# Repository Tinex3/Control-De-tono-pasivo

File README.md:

# Control de Tono para Canales de Audio R y L

## Descripción

Proyecto básico de control de tono discreto para los canales de audio derecho (R) e izquierdo (L). Utiliza resistencias, condensadores, potenciómetros y conectores JST XH para ajustes simples de bajos, agudos y volumen en dispositivos de audio.

## Componentes

- Resistencias
- Condensadores
- Potenciómetros
- Conectores JST XH

## Uso

Ajusta fácilmente los niveles de bajos, agudos y volumen general.

## Autor

- Autor: Benjamin Riquelme
- Correo electrónico: b.riquelme.gomez@gmail.com

## Licencia

Licencia MIT. Consulta el archivo LICENSE.md para más detalles.

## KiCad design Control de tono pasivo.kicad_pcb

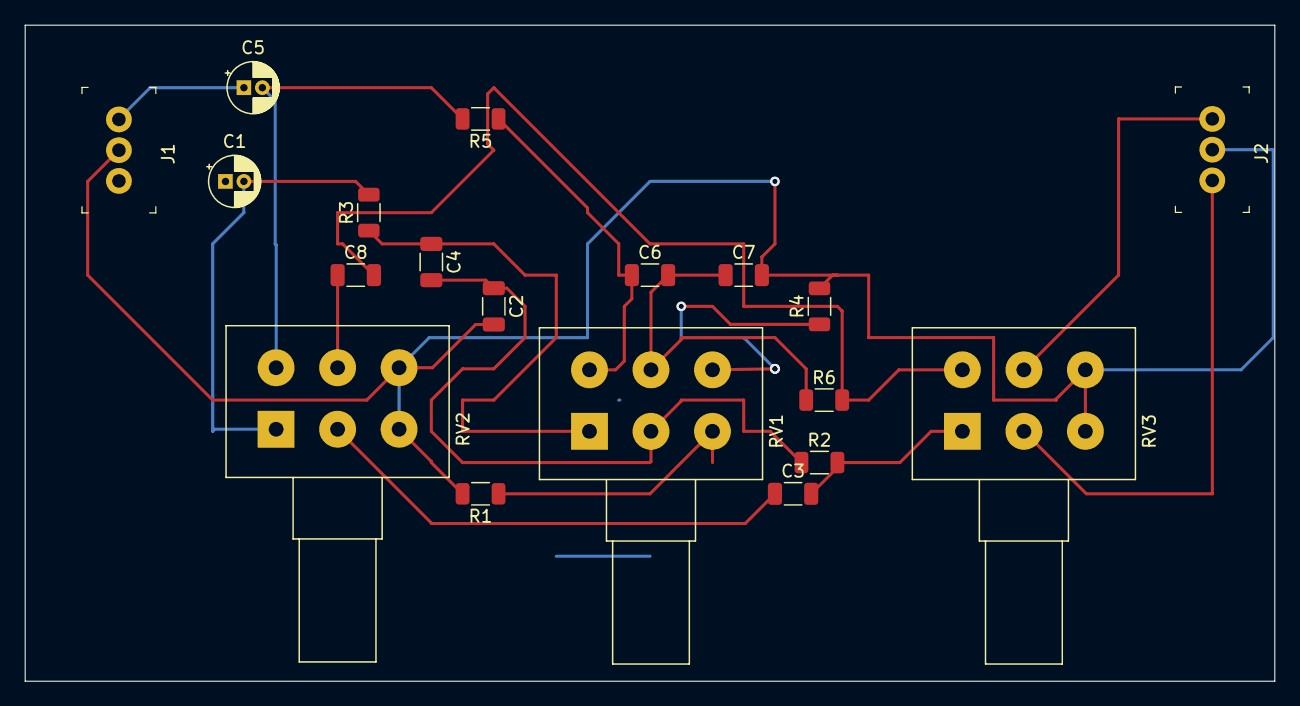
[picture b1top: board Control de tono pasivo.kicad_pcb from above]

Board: 2 copper layers, 101.6 x 53.3 mm, 19 parts (0 on the bottom side), 17 nets.

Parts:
C1: C; CP_Radial_D4.0mm_P1.50mm
C2, C4, C6, C7: 47n; C_1206_3216Metric
C3, C8: 10n; C_1206_3216Metric
C5: 100u; CP_Radial_D4.0mm_P1.50mm
J1, J2: B3B-XH-A_LF__SN_; PinHeader_1x3_P2.5mm_Drill1.1mm
R1, R4, R5: 4k7; R_1206_3216Metric
R2, R6: 560; R_1206_3216Metric
R3: 4K7; R_1206_3216Metric
RV1, RV2: 10k; Potentiometer_Alps_RK163_Dual_Horizontal
RV3: 20k; Potentiometer_Alps_RK163_Dual_Horizontal

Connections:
/L: C5.1, J1.1
/Output L: J2.1, RV3.5
/Output R: J2.3, RV3.2
/R: C1.1, J1.3
GND: C2.2, C7.2, J1.2, J2.2, R1.2, R4.2, RV2.3, RV2.6, RV3.3, RV3.6
unnamed: C1.2, R3.2, RV2.1
unnamed: C2.1, C4.2, R2.1, RV1.2
unnamed: C3.1, RV2.2
unnamed: C3.2, R2.2, RV3.1
unnamed: C4.1, R3.1, RV1.1
unnamed: C5.2, R5.2, RV2.4
unnamed: C6.1, R5.1, RV1.4
unnamed: C6.2, C7.1, R6.1, RV1.5
unnamed: C8.1, RV2.5
unnamed: C8.2, R6.2, RV3.4
unnamed: R1.1, RV1.3
unnamed: R4.1, RV1.6

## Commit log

2024-01-16 Control de tono pasivo para audio
